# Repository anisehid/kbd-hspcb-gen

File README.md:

Generate PCB with layout description file

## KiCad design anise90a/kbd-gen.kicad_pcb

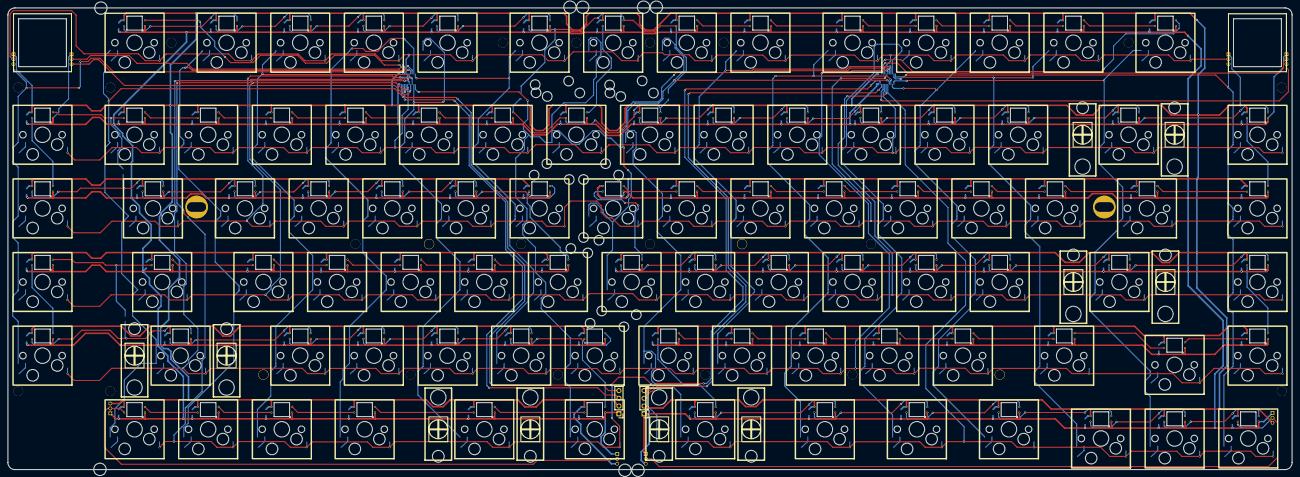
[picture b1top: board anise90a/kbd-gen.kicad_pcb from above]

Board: 2 copper layers, 332.2 x 119.4 mm, 98 parts (0 on the bottom side), 116 nets.

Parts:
CN1, CN2: BTB; 30PIN_0.4MM_BTB_MALE
HOLE: VAL**; PKRHC
HOLE#2, HOLE#5: VAL**; PKRHSL
HOLE#3, HOLE#4: VAL**; PKRHC
P1, P2: P; PinHeader_1x04_P2.00mm_Vertical
S11, S12, S13, S14, S15, S16, S17, S18, S19, S20, S21, S22, S23, S24, S25, S26, S27, S28, S29, S30, S31, S32, S33, S34, S35, S36, S37, S38, S39, S40, S41, S42, S43, S44, S45, S46, S47, S48, S49, S50, S51, S53, S54, S55, S56, S57, S58, S59, S61, S62, S63, S64, S65, S67, S68, S110, S111, S112, S113, S114, S210, S211, S212, S213, S214, S215, S310, S311, S312, S313, S314, S315, S410, S411, S412, S414, S415, S510, S511, S512, S513, S514, S515, S610, S611, S612, S613, S614, S615: MX_LED; MXHS-1U-RGB-ALI-3528-HOLE-NOPAD

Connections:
GND: CN1.2, CN1.34, CN2.2, CN2.34, P1.1, P2.1, S11.CN, S11.GND, S12.CN, S12.GND, S13.CN, S13.GND, S14.CN, S14.GND, S15.CN, S15.GND, S16.CN, S16.GND, S17.CN, S17.GND, S18.CN, S18.GND, S19.CN, S19.GND, S20.CN, S20.GND, S21.CN, S21.GND, S22.CN, S22.GND, S23.CN, S23.GND, S24.CN, S24.GND, S25.CN, S25.GND, S26.CN, S26.GND, S27.CN, S27.GND, S28.CN, S28.GND, S29.CN, S29.GND, S30.CN, S30.GND, S31.CN, S31.GND, S32.CN, S32.GND, S33.CN, S33.GND, S34.CN, S34.GND, S35.CN, S35.GND, S36.CN, S36.GND, S37.CN, S37.GND, S38.CN, S38.GND, S39.CN, S39.GND, S40.CN, S40.GND, S41.CN, S41.GND, S42.CN, S42.GND, S43.CN, S43.GND, S44.CN, S44.GND, S45.CN, S45.GND, S46.CN, S46.GND, S47.CN, S47.GND, S48.CN, S48.GND, S49.CN, S49.GND, S50.CN, S50.GND, S51.CN, S51.GND, S53.CN, S53.GND, S54.CN, S54.GND, S55.CN, S55.GND, S56.CN, S56.GND, S57.CN, S57.GND, S58.CN, S58.GND, S59.CN, S59.GND, S61.CN, S61.GND, S62.CN, S62.GND, S63.CN, S63.GND, S64.CN, S64.GND, S65.CN, S65.GND, S67.CN, S67.GND, S68.CN, S68.GND, S110.CN, S110.GND, S111.CN, S111.GND, S112.CN, S112.GND, S113.CN, S113.GND, S114.CN, S114.GND, S210.CN, S210.GND, S211.CN, S211.GND, S212.CN, S212.GND, S213.CN, S213.GND, S214.CN, S214.GND, S215.CN, S215.GND, S310.CN, S310.GND, S311.CN, S311.GND, S312.CN, S312.GND, S313.CN, S313.GND, S314.CN, S314.GND, S315.CN, S315.GND, S410.CN, S410.GND, S411.CN, S411.GND, S412.CN, S412.GND, S414.CN, S414.GND, S415.CN, S415.GND, S510.CN, S510.GND, S511.CN, S511.GND, S512.CN, S512.GND, S513.CN, S513.GND, S514.CN, S514.GND, S515.CN, S515.GND, S610.CN, S610.GND, S611.CN, S611.GND, S612.CN, S612.GND, S613.CN, S613.GND, S614.CN, S614.GND, S615.CN, S615.GND
S11_12: S11.DO, S12.DI
S12_13: S12.DO, S13.DI
S13_14: S13.DO, S14.DI
S14_15: S14.DO, S15.DI
S15_16: S15.DO, S16.DI
S17_27_1: S17.DO, S27.DI
S18_17: S16.DO, S17.DI, S18.DO
S19_18: S18.DI, S19.DO
S20_30: S20.DO, S30.DI
S21_20: S20.DI, S21.DO
S22_21: S21.DI, S22.DO
S23_22: S22.DI, S23.DO
S24_23: S23.DI, S24.DO
S25_24: S24.DI, S25.DO
S26_25: S25.DI, S26.DO
S27_26: S26.DI, S27.DO, S28.DI
S28_29: S28.DO, S29.DI
S29_210: S29.DO, S210.DI
S30_31: S30.DO, S31.DI
S31_32: S31.DO, S32.DI
S32_33: S32.DO, S33.DI
S33_34: S33.DO, S34.DI
S34_35: S34.DO, S35.DI
S35_36: S35.DO, S36.DI
S36_46: S36.DO, S46.DI
S37_47: S37.DO, S47.DI
S38_37: S37.DI, S38.DO
S39_38: S38.DI, S39.DO
S40_50: S40.DO, S50.DI
S41_40: S40.DI, S41.DO
S42_41: S41.DI, S42.DO
S43_42: S42.DI, S43.DO
S44_43: S43.DI, S44.DO
S45_44: S44.DI, S45.DO
S46_45: S45.DI, S46.DO
S47_48: S47.DO, S48.DI
S48_49: S48.DO, S49.DI
S49_410: S49.DO, S410.DI
S50_51: S50.DO, S51.DI
S51_53: S51.DO, S53.DI
S53_54: S53.DO, S54.DI
S54_55: S54.DO, S55.DI
S55_56: S55.DO, S56.DI
S56_57: S56.DO, S57.DI
S57_67: S57.DO, S67.DI
S58_68: S58.DO, S68.DI
S59_58: S58.DI, S59.DO
S62_61: S61.DI, S62.DO
S63_62: S62.DI, S63.DO
S64_63: S63.DI, S64.DO
S65_64: S64.DI, S65.DO
S67_65: S65.DI, S67.DO
S68_610: S68.DO, S610.DI
S110_19: S19.DI, S110.DO
S111_110: S110.DI, S111.DO
S112_111: S111.DI, S112.DO
S113_112: S112.DI, S113.DO
S114_113: S113.DI, S114.DO
S210_211: S210.DO, S211.DI
S211_212: S211.DO, S212.DI
S212_213: S212.DO, S213.DI
S213_214: S213.DO, S214.DI
S214_215: S214.DO, S215.DI
S215_315: S215.DO, S315.DI
S310_39: S39.DI, S310.DO
S311_310: S310.DI, S311.DO
S312_311: S311.DI, S312.DO
S313_312: S312.DI, S313.DO
S314_313: S313.DI, S314.DO
S315_314: S314.DI, S315.DO
S410_411: S410.DO, S411.DI
S411_412: S411.DO, S412.DI
S412_414: S412.DO, S414.DI
S414_415: S414.DO, S415.DI
S415_515: S415.DO, S515.DI
S510_59: S59.DI, S510.DO
S511_510: S510.DI, S511.DO
S512_511: S511.DI, S512.DO
S513_512: S512.DI, S513.DO
S514_513: S513.DI, S514.DO
S515_514: S514.DI, S515.DO
S610_611: S610.DO, S611.DI
S611_612: S611.DO, S612.DI
S612_613: S612.DO, S613.DI
S613_614: S613.DO, S614.DI
S614_615: S614.DO, S615.DI
VCC: CN1.1, CN1.33, CN2.1, CN2.33, P1.2, P2.2, S11.CP, S11.VCC, S12.CP, S12.VCC, S13.CP, S13.VCC, S14.CP, S14.VCC, S15.CP, S15.VCC, S16.CP, S16.VCC, S17.CP, S17.VCC, S18.CP, S18.VCC, S19.CP, S19.VCC, S20.CP, S20.VCC, S21.CP, S21.VCC, S22.CP, S22.VCC, S23.CP, S23.VCC, S24.CP, S24.VCC, S25.CP, S25.VCC, S26.CP, S26.VCC, S27.CP, S27.VCC, S28.CP, S28.VCC, S29.CP, S29.VCC, S30.CP, S30.VCC, S31.CP, S31.VCC, S32.CP, S32.VCC, S33.CP, S33.VCC, S34.CP, S34.VCC, S35.CP, S35.VCC, S36.CP, S36.VCC, S37.CP, S37.VCC, S38.CP, S38.VCC, S39.CP, S39.VCC, S40.CP, S40.VCC, S41.CP, S41.VCC, S42.CP, S42.VCC, S43.CP, S43.VCC, S44.CP, S44.VCC, S45.CP, S45.VCC, S46.CP, S46.VCC, S47.CP, S47.VCC, S48.CP, S48.VCC, S49.CP, S49.VCC, S50.CP, S50.VCC, S51.CP, S51.VCC, S53.CP, S53.VCC, S54.CP, S54.VCC, S55.CP, S55.VCC, S56.CP, S56.VCC, S57.CP, S57.VCC, S58.CP, S58.VCC, S59.CP, S59.VCC, S61.CP, S61.VCC, S62.CP, S62.VCC, S63.CP, S63.VCC, S64.CP, S64.VCC, S65.CP, S65.VCC, S67.CP, S67.VCC, S68.CP, S68.VCC, S110.CP, S110.VCC, S111.CP, S111.VCC, S112.CP, S112.VCC, S113.CP, S113.VCC, S114.CP, S114.VCC, S210.CP, S210.VCC, S211.CP, S211.VCC, S212.CP, S212.VCC, S213.CP, S213.VCC, S214.CP, S214.VCC, S215.CP, S215.VCC, S310.CP, S310.VCC, S311.CP, S311.VCC, S312.CP, S312.VCC, S313.CP, S313.VCC, S314.CP, S314.VCC, S315.CP, S315.VCC, S410.CP, S410.VCC, S411.CP, S411.VCC, S412.CP, S412.VCC, S414.CP, S414.VCC, S415.CP, S415.VCC, S510.CP, S510.VCC, S511.CP, S511.VCC, S512.CP, S512.VCC, S513.CP, S513.VCC, S514.CP, S514.VCC, S515.CP, S515.VCC, S610.CP, S610.VCC, S611.CP, S611.VCC, S612.CP, S612.VCC, S613.CP, S613.VCC, S614.CP, S614.VCC, S615.CP, S615.VCC
c0: CN1.15, S20.1, S30.1, S40.1, S50.1
c1: CN1.16, S11.1, S21.1, S31.1, S41.1, S51.1, S61.1
c2: CN1.17, S12.1, S22.1, S32.1, S42.1, S62.1
c3: CN1.18, S13.1, S23.1, S33.1, S43.1, S53.1, S63.1
c4: CN1.19, S14.1, S24.1, S34.1, S44.1, S54.1, S64.1
c5: CN1.20, S15.1, S25.1, S35.1, S45.1, S55.1, S65.1
c6: CN1.21, S16.1, S26.1, S36.1, S46.1, S56.1
c7: CN1.22, CN2.15, S17.1, S27.1, S37.1, S47.1, S57.1, S67.1
c8: CN2.16, S18.1, S28.1, S38.1, S48.1, S58.1, S68.1
c9: CN2.17, S19.1, S29.1, S39.1, S49.1, S59.1
c10: CN2.18, S110.1, S210.1, S310.1, S410.1, S510.1, S610.1
c11: CN2.19, S111.1, S211.1, S311.1, S411.1, S511.1, S611.1
c12: CN2.20, S112.1, S212.1, S312.1, S412.1, S512.1, S612.1
c13: CN2.21, S113.1, S213.1, S313.1, S513.1, S613.1
c14: CN2.22, S114.1, S214.1, S314.1, S414.1, S514.1, S614.1
c15: CN2.23, S215.1, S315.1, S415.1, S515.1, S615.1
led1_11: CN1.5, S11.DI
led2_114: CN2.5, S114.DI
r1: CN1.9, CN2.9, S11.2, S12.2, S13.2, S14.2, S15.2, S16.2, S17.2, S18.2, S19.2, S110.2, S111.2, S112.2, S113.2, S114.2
r2: CN1.10, CN2.10, S20.2, S21.2, S22.2, S23.2, S24.2, S25.2, S26.2, S27.2, S28.2, S29.2, S210.2, S211.2, S212.2, S213.2, S214.2, S215.2
r3: CN1.11, CN2.11, S30.2, S31.2, S32.2, S33.2, S34.2, S35.2, S36.2, S37.2, S38.2, S39.2, S310.2, S311.2, S312.2, S313.2, S314.2, S315.2
r4: CN1.12, CN2.12, S40.2, S41.2, S42.2, S43.2, S44.2, S45.2, S46.2, S47.2, S48.2, S49.2, S410.2, S411.2, S412.2, S414.2, S415.2
r5: CN1.13, CN2.13, S50.2, S51.2, S53.2, S54.2, S55.2, S56.2, S57.2, S58.2, S59.2, S510.2, S511.2, S512.2, S513.2, S514.2, S515.2
r6: CN1.14, CN2.14, S61.2, S62.2, S63.2, S64.2, S65.2, S67.2, S68.2, S610.2, S611.2, S612.2, S613.2, S614.2, S615.2
sclL: CN1.6, P1.3
sclR: CN2.6, P2.3
sdaL: CN1.4, P1.4
sdaR: CN2.4, P2.4

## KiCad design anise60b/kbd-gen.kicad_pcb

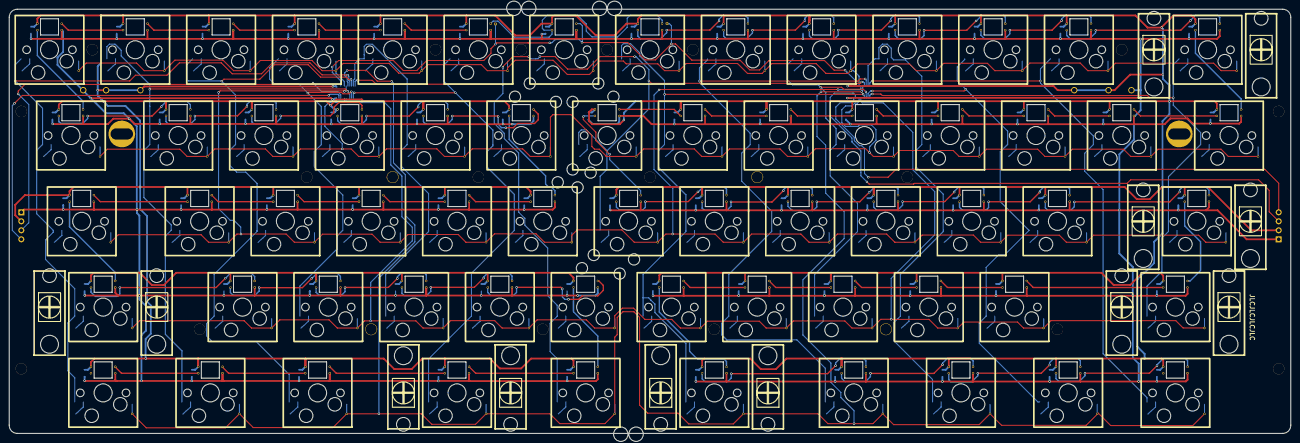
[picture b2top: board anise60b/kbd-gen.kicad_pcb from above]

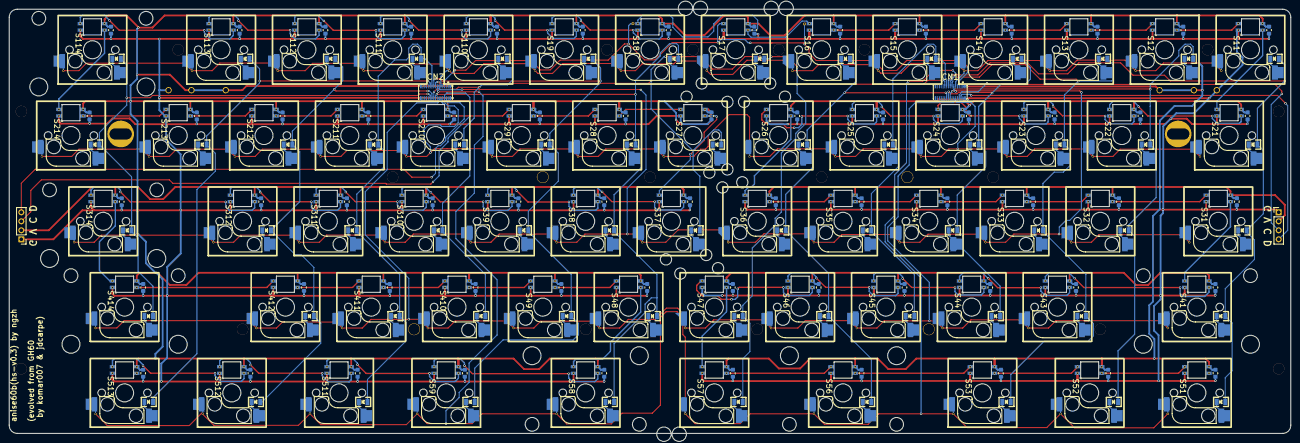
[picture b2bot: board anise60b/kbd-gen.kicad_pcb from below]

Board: 2 copper layers, 284.6 x 94.2 mm, 72 parts (2 on the bottom side), 87 nets.

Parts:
CN1, CN2: BTB; 30PIN_0.4MM_BTB_MALE
HOLE: VAL**; PKRHC
HOLE#2, HOLE#5: VAL**; PKRHSL
HOLE#3: VAL**; PKRHC
HOLE#4: VAL**; PKRH
P1, P2: P; PinHeader_1x04_P2.00mm_Vertical
S11, S12, S13, S14, S15, S16, S17, S18, S19, S21, S22, S23, S24, S25, S26, S27, S28, S29, S31, S32, S33, S34, S35, S36, S37, S38, S39, S41, S43, S44, S45, S46, S47, S48, S49, S51, S52, S53, S56, S57, S58, S59, S110, S111, S112, S113, S114, S210, S211, S212, S213, S214, S310, S311, S312, S314, S410, S411, S412, S414, S511, S512, S513: MX_LED; MXHS-1U-RGB-ALI-3528-HOLE-NOPAD

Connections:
GND: CN1.2, CN2.2, P1.1, P2.1, S11.CN, S11.GND, S12.CN, S12.GND, S13.CN, S13.GND, S14.CN, S14.GND, S15.CN, S15.GND, S16.CN, S16.GND, S17.CN, S17.GND, S18.CN, S18.GND, S19.CN, S19.GND, S21.CN, S21.GND, S22.CN, S22.GND, S23.CN, S23.GND, S24.CN, S24.GND, S25.CN, S25.GND, S26.CN, S26.GND, S27.CN, S27.GND, S28.CN, S28.GND, S29.CN, S29.GND, S31.CN, S31.GND, S32.CN, S32.GND, S33.CN, S33.GND, S34.CN, S34.GND, S35.CN, S35.GND, S36.CN, S36.GND, S37.CN, S37.GND, S38.CN, S38.GND, S39.CN, S39.GND, S41.CN, S41.GND, S43.CN, S43.GND, S44.CN, S44.GND, S45.CN, S45.GND, S46.CN, S46.GND, S47.CN, S47.GND, S48.CN, S48.GND, S49.CN, S49.GND, S51.CN, S51.GND, S52.CN, S52.GND, S53.CN, S53.GND, S56.CN, S56.GND, S57.CN, S57.GND, S58.CN, S58.GND, S59.CN, S59.GND, S110.CN, S110.GND, S111.CN, S111.GND, S112.CN, S112.GND, S113.CN, S113.GND, S114.CN, S114.GND, S210.CN, S210.GND, S211.CN, S211.GND, S212.CN, S212.GND, S213.CN, S213.GND, S214.CN, S214.GND, S310.CN, S310.GND, S311.CN, S311.GND, S312.CN, S312.GND, S314.CN, S314.GND, S410.CN, S410.GND, S411.CN, S411.GND, S412.CN, S412.GND, S414.CN, S414.GND, S511.CN, S511.GND, S512.CN, S512.GND, S513.CN, S513.GND
S11_21: S11.DO, S21.DI
S12_11: S11.DI, S12.DO
S13_12: S12.DI, S13.DO
S14_13: S13.DI, S14.DO
S15_14: S14.DI, S15.DO
S16_15: S15.DI, S16.DO
S17_18: S16.DI, S17.DO, S18.DI
S18_19: S18.DO, S19.DI
S19_110: S19.DO, S110.DI
S21_22: S21.DO, S22.DI
S22_23: S22.DO, S23.DI
S23_24: S23.DO, S24.DI
S24_25: S24.DO, S25.DI
S25_26: S25.DO, S26.DI
S26_36: S26.DO, S36.DI
S27_37: S27.DO, S37.DI
S28_27: S27.DI, S28.DO
S29_28: S28.DI, S29.DO
S31_41: S31.DO, S41.DI
S32_31: S31.DI, S32.DO
S33_32: S32.DI, S33.DO
S34_33: S33.DI, S34.DO
S35_34: S34.DI, S35.DO
S36_35: S35.DI, S36.DO
S37_38: S37.DO, S38.DI
S38_39: S38.DO, S39.DI
S39_310: S39.DO, S310.DI
S41_43: S41.DO, S43.DI
S43_44: S43.DO, S44.DI
S44_45: S44.DO, S45.DI
S45_46: S45.DO, S46.DI
S46_47: S46.DO, S47.DI
S47_57: S47.DO, S57.DI
S48_58: S48.DO, S58.DI
S49_48: S48.DI, S49.DO
S52_51: S51.DI, S52.DO
S53_52: S52.DI, S53.DO
S56_53: S53.DI, S56.DO
S57_56: S56.DI, S57.DO
S58_59: S58.DO, S59.DI
S59_511: S59.DO, S511.DI
S110_111: S110.DO, S111.DI
S111_112: S111.DO, S112.DI
S112_113: S112.DO, S113.DI
S113_114: S113.DO, S114.DI
S114_214: S114.DO, S214.DI
S210_29: S29.DI, S210.DO
S211_210: S210.DI, S211.DO
S212_211: S211.DI, S212.DO
S213_212: S212.DI, S213.DO
S214_213: S213.DI, S214.DO
S310_311: S310.DO, S311.DI
S311_312: S311.DO, S312.DI
S312_314: S312.DO, S314.DI
S314_414: S314.DO, S414.DI
S410_49: S49.DI, S410.DO
S411_410: S410.DI, S411.DO
S412_411: S411.DI, S412.DO
S414_412: S412.DI, S414.DO
S511_512: S511.DO, S512.DI
S512_513: S512.DO, S513.DI
VCC: CN1.1, CN2.1, P1.2, P2.2, S11.CP, S11.VCC, S12.CP, S12.VCC, S13.CP, S13.VCC, S14.CP, S14.VCC, S15.CP, S15.VCC, S16.CP, S16.VCC, S17.CP, S17.VCC, S18.CP, S18.VCC, S19.CP, S19.VCC, S21.CP, S21.VCC, S22.CP, S22.VCC, S23.CP, S23.VCC, S24.CP, S24.VCC, S25.CP, S25.VCC, S26.CP, S26.VCC, S27.CP, S27.VCC, S28.CP, S28.VCC, S29.CP, S29.VCC, S31.CP, S31.VCC, S32.CP, S32.VCC, S33.CP, S33.VCC, S34.CP, S34.VCC, S35.CP, S35.VCC, S36.CP, S36.VCC, S37.CP, S37.VCC, S38.CP, S38.VCC, S39.CP, S39.VCC, S41.CP, S41.VCC, S43.CP, S43.VCC, S44.CP, S44.VCC, S45.CP, S45.VCC, S46.CP, S46.VCC, S47.CP, S47.VCC, S48.CP, S48.VCC, S49.CP, S49.VCC, S51.CP, S51.VCC, S52.CP, S52.VCC, S53.CP, S53.VCC, S56.CP, S56.VCC, S57.CP, S57.VCC, S58.CP, S58.VCC, S59.CP, S59.VCC, S110.CP, S110.VCC, S111.CP, S111.VCC, S112.CP, S112.VCC, S113.CP, S113.VCC, S114.CP, S114.VCC, S210.CP, S210.VCC, S211.CP, S211.VCC, S212.CP, S212.VCC, S213.CP, S213.VCC, S214.CP, S214.VCC, S310.CP, S310.VCC, S311.CP, S311.VCC, S312.CP, S312.VCC, S314.CP, S314.VCC, S410.CP, S410.VCC, S411.CP, S411.VCC, S412.CP, S412.VCC, S414.CP, S414.VCC, S511.CP, S511.VCC, S512.CP, S512.VCC, S513.CP, S513.VCC
c1: CN1.15, S11.1, S21.1, S31.1, S41.1, S51.1
c2: CN1.16, S12.1, S22.1, S32.1, S52.1
c3: CN1.17, S13.1, S23.1, S33.1, S43.1, S53.1
c4: CN1.18, S14.1, S24.1, S34.1, S44.1
c5: CN1.19, S15.1, S25.1, S35.1, S45.1
c6: CN1.20, S16.1, S26.1, S36.1, S46.1, S56.1
c7: CN1.21, CN2.15, S17.1, S27.1, S37.1, S47.1, S57.1
c8: CN2.16, S18.1, S28.1, S38.1, S48.1, S58.1
c9: CN2.17, S19.1, S29.1, S39.1, S49.1, S59.1
c10: CN2.18, S110.1, S210.1, S310.1, S410.1
c11: CN2.19, S111.1, S211.1, S311.1, S411.1, S511.1
c12: CN2.20, S112.1, S212.1, S312.1, S412.1, S512.1
c13: CN2.21, S113.1, S213.1, S513.1
c14: CN2.22, S114.1, S214.1, S314.1, S414.1
led1_17: CN1.5, CN2.5, S17.DI
r1: CN1.9, CN2.9, S11.2, S12.2, S13.2, S14.2, S15.2, S16.2, S17.2, S18.2, S19.2, S110.2, S111.2, S112.2, S113.2, S114.2
r2: CN1.10, CN2.10, S21.2, S22.2, S23.2, S24.2, S25.2, S26.2, S27.2, S28.2, S29.2, S210.2, S211.2, S212.2, S213.2, S214.2
r3: CN1.11, CN2.11, S31.2, S32.2, S33.2, S34.2, S35.2, S36.2, S37.2, S38.2, S39.2, S310.2, S311.2, S312.2, S314.2
r4: CN1.12, CN2.12, S41.2, S43.2, S44.2, S45.2, S46.2, S47.2, S48.2, S49.2, S410.2, S411.2, S412.2, S414.2
r5: CN1.13, CN2.13, S51.2, S52.2, S53.2, S56.2, S57.2, S58.2, S59.2, S511.2, S512.2, S513.2
sclL: CN1.6, P1.3
sclR: CN2.6, P2.3
sdaL: CN1.4, P1.4
sdaR: CN2.4, P2.4

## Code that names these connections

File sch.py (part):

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    nets["sclL"] = Net("sclL")
    nets["GND"] += pinheader_left["1"]
    nets["VCC"] += pinheader_left["2"]
    nets["sclL"] += pinheader_left["3"]
    nets["sdaL"] += pinheader_left["4"]
    nets["GND"] += pinheader_right["1"]
    nets["VCC"] += pinheader_right["2"]
    nets["sclR"] += pinheader_right["3"]
    nets["sdaR"] += pinheader_right["4"]

    # conn generation
    btb_conns = []
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
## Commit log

2022-07-12 generate netlist basicly ok
2022-07-12 basicly ok
2022-07-13 first pcb hsdefault rollout
2022-07-13 bom/pos generation ok
2022-07-24 update kbd-default
2022-09-03 update anysplit60-dnav
2022-09-06 add more layout
2022-11-01 update with anise90 seris/ outline and holes are not fully ready
2023-02-24 update for 24 Feb 2023 release
2023-02-24 add README and license
